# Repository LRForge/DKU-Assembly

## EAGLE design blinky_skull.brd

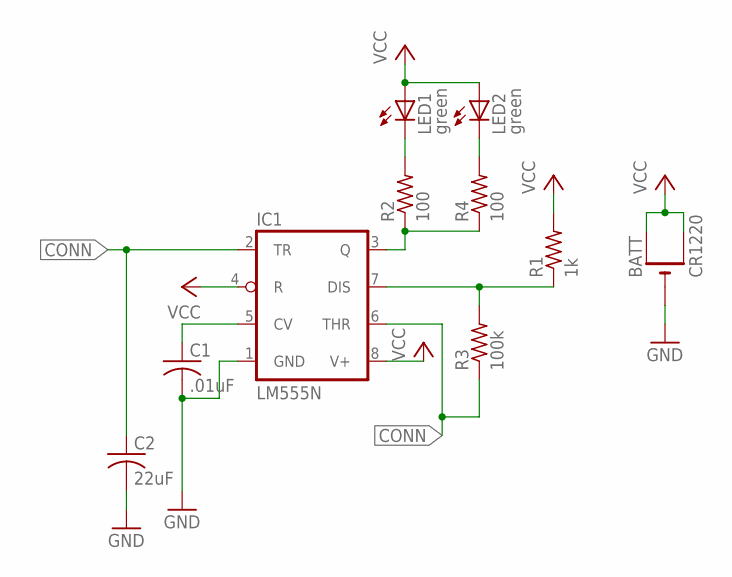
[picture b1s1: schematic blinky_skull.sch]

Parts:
BATT: CR1220; CR1220-SMD
C1: .01uF; C0805
C2: 22uF; C0805
IC1: LM555N; DIL08-ROUND
LED1, LED2: green; LED5MM
R1: 1k; R0805
R2, R4: 100; R0805
R3: 100k; R0805

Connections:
CONN: C2.1, IC1.2 (TR), IC1.6 (THR), R3.1
GND: BATT.-, C1.2, C2.2, IC1.1 (GND)
unnamed: LED1.K (C), R2.2
unnamed: IC1.3 (Q), R2.1, R4.1
unnamed: LED2.K (C), R4.2
unnamed: IC1.7 (DIS), R1.1, R3.2
unnamed: C1.1, IC1.5 (CV)
VCC: BATT.+$1 (+), BATT.+$2 (+1), IC1.4 (R), IC1.8 (V+), LED1.A, LED2.A, R1.2

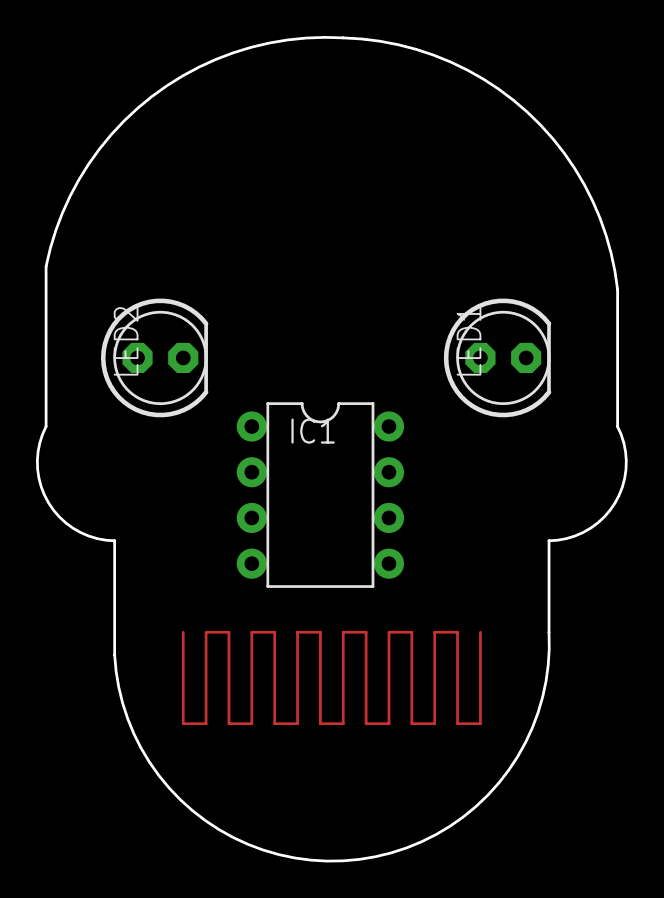
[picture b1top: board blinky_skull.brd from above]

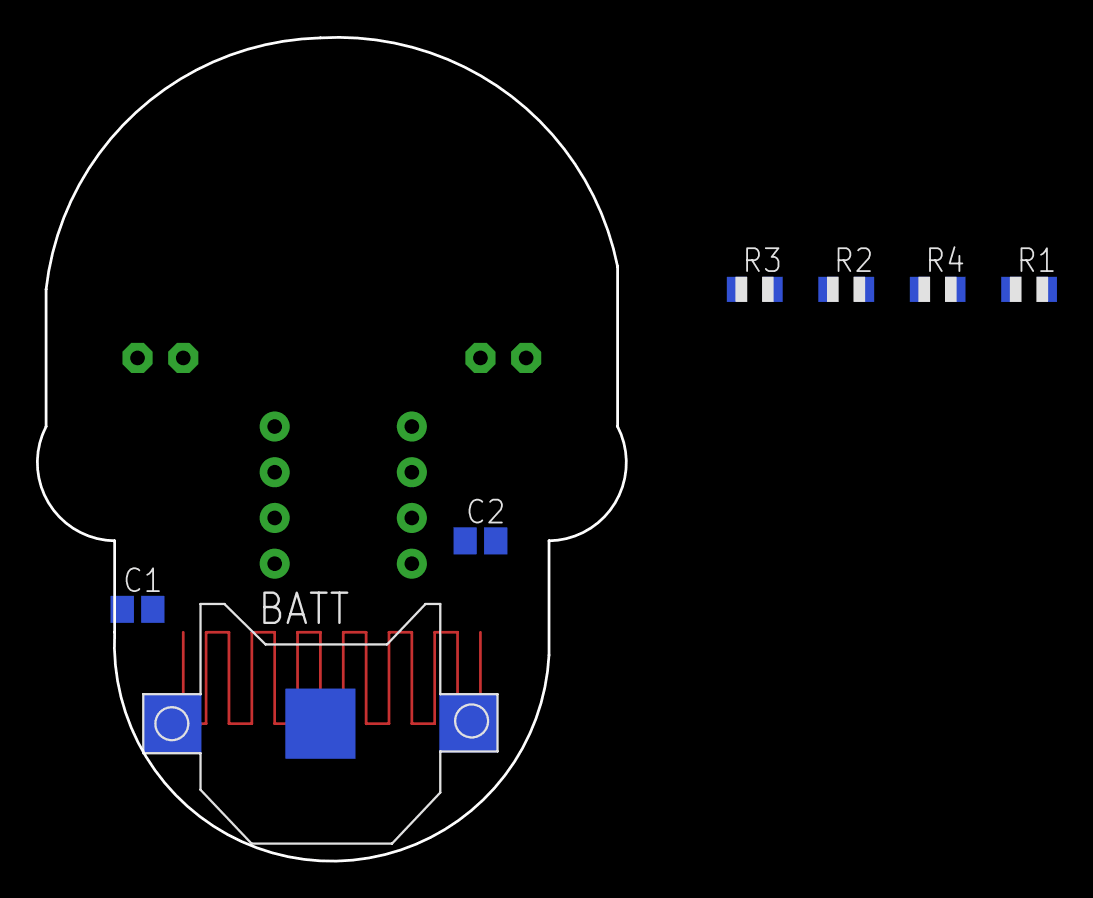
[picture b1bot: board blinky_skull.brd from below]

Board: 2 copper layers, 32.7 x 45.8 mm, 10 parts (7 on the bottom side), 8 nets.
